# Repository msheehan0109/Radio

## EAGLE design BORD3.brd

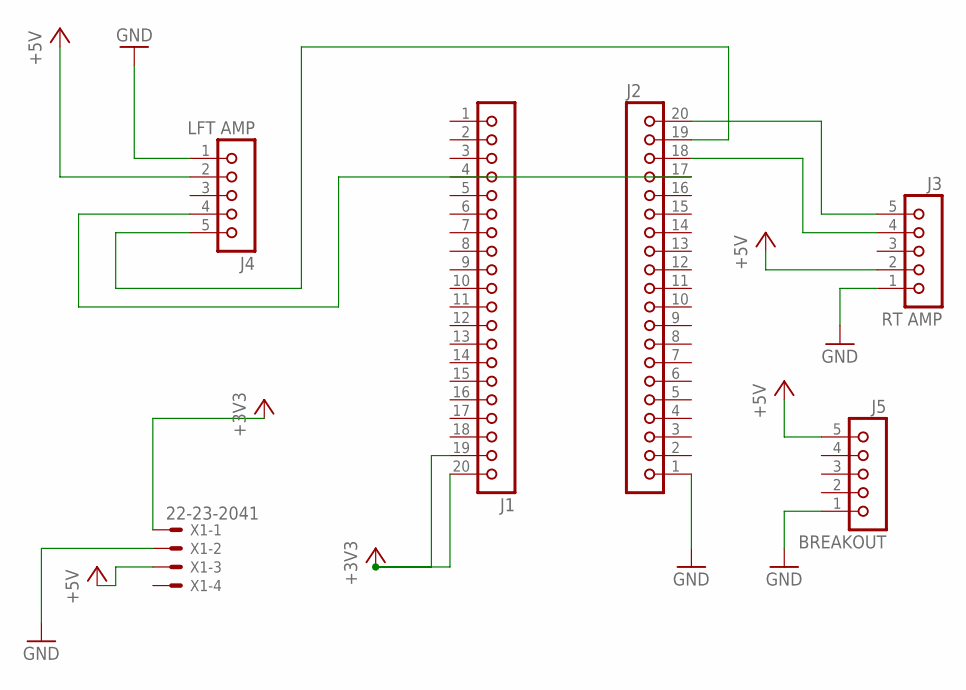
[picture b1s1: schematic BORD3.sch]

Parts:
J1, J2: JBK20
J3: RT AMP; JU05
J4: LFT AMP; JU05
J5: BREAKOUT; JU05
X1: 22-23-2041

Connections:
+3V3: J1.19, J1.20, X1.1
+5V: J3.2, J4.2, J5.5, X1.3
GND: J2.1, J3.1, J4.1, J5.1, X1.2
unnamed: J2.19, J4.5
unnamed: J2.20, J3.5
unnamed: J2.17, J4.4
unnamed: J2.18, J3.4

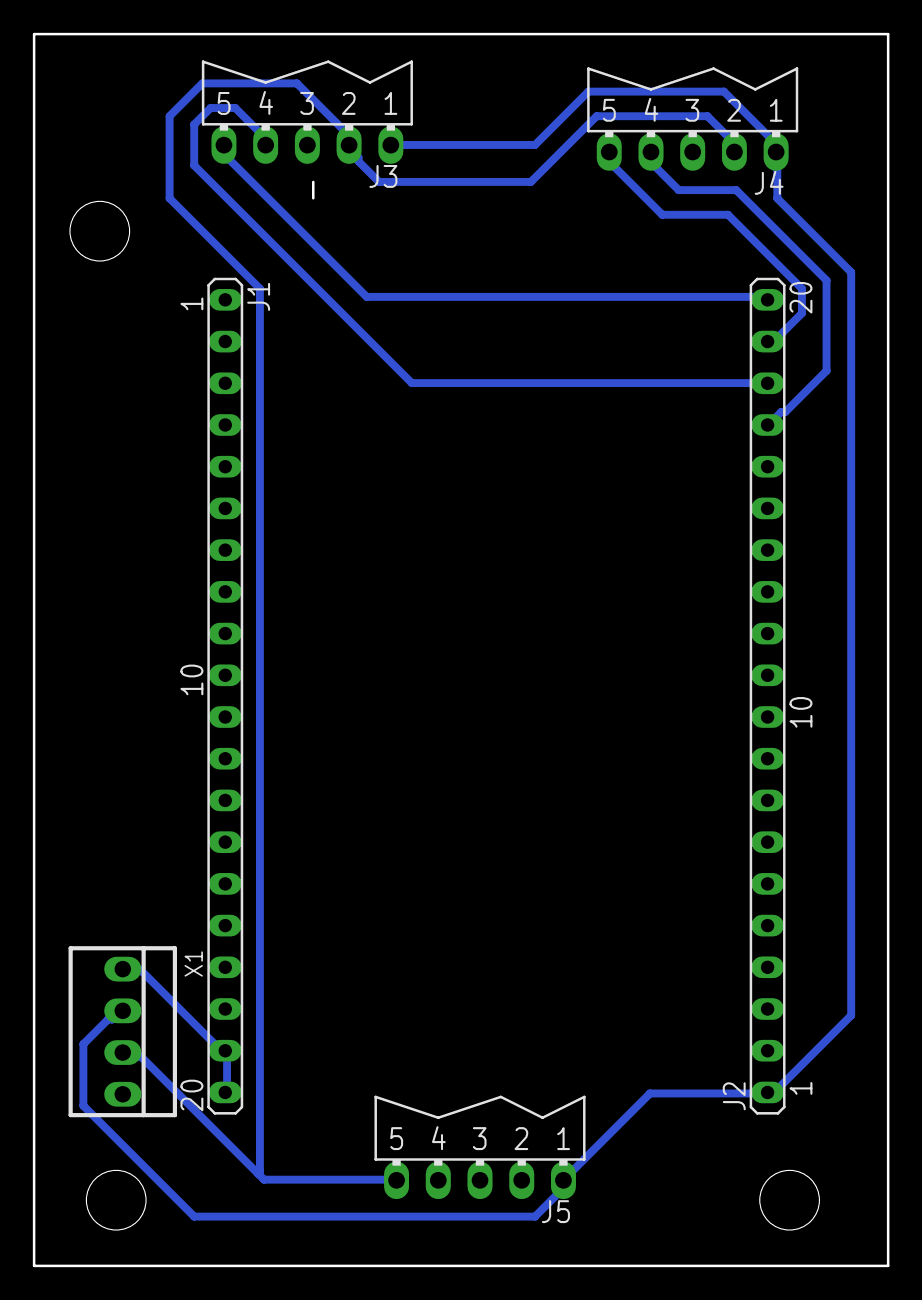
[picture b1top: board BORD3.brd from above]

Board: 2 copper layers, 52.0 x 75.0 mm, 6 parts (0 on the bottom side), 7 nets.
